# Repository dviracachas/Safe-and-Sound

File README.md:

# Intercomunicador Safe & Sound 🏍
En este repositorio se encuentra el desarrollo de la propuesta de proyecto realizada para la asignatura de Sistemas Embebidos de la Universidad Nacional de Colombia, la cual consiste en un intercomunicador para motocicletas que cuente con funcionalidades orientadas a la seguridad de sus usuarios.

## Equipo de trabajo
* Juan Gabriel Barrera Barrera
* Juan José Forero Bernal
* Camilo Andrés Jaimes Reyes
* David Santiago Viracachá Suárez

## Descripción general
El intercomunicador Safe & Sound es un producto para motociclistas que buscan comunicarse con sus pasajeros o hacer uso de funciones de audio por medio de su teléfono celular, como lo puede ser recibir indicaciones de alguna aplicación de mapas. Además, es un producto que busca la seguridad del usuario, emitiendo alertas de velocidad e implementando detección de accidentes para realizar llamadas de emergencia haciendo uso del teléfono.

## Requerimientos funcionales
* Conectarse a otro dispositivo igual o un teléfono mediante Bluetooth
* Transmitir y/o recibir audio con los dispositivos conectados
* Procesamiento de señales dadas por sensores
* Emitir alertas de velocidad al usuario
* Detectar cambios repentinos de velocidad
* Comunicación con emergencias por medio de conexión con celular

## Requerimientos no funcionales
* Dispositivo pequeño adaptable a cascos para motocicletas
* Amigable al usuario
* Duración de la batería
* Cumplir con estándares de audio Bluetooth y compatibilidad electromagnética
* Cumplir con normas establecidas para circuitos impresos

## Diagrama de bloques

## Diagrama de funcionamiento
[Diagrama de funcionamiento](Imagenes/Funcionamiento_safe_and_sound.pdf)

### Descripción del Hardware
Una vez identificadas las funciones y los requerimientos del intercomunicador a realizar se escogen los compontes básicos, estos son:

Componentes Básicos:
* ESP32-WROOM-32
* Acelerómetro ADXL335.
* Batería de litio de 3.7V y 280mAh.
* Amplificador de Audio MAX98357 I2S 3W clase D
* Módulo Micrófono Mems I2s Inmp441
* Mini Altavoces.
* Conectores de diversos tipos.
* Resistores.
* Capacitores
* Potenciómetro.
* Pulsadores.
* Leds.
* Conector Micro-USB hembra.
* Switch Deslizante.

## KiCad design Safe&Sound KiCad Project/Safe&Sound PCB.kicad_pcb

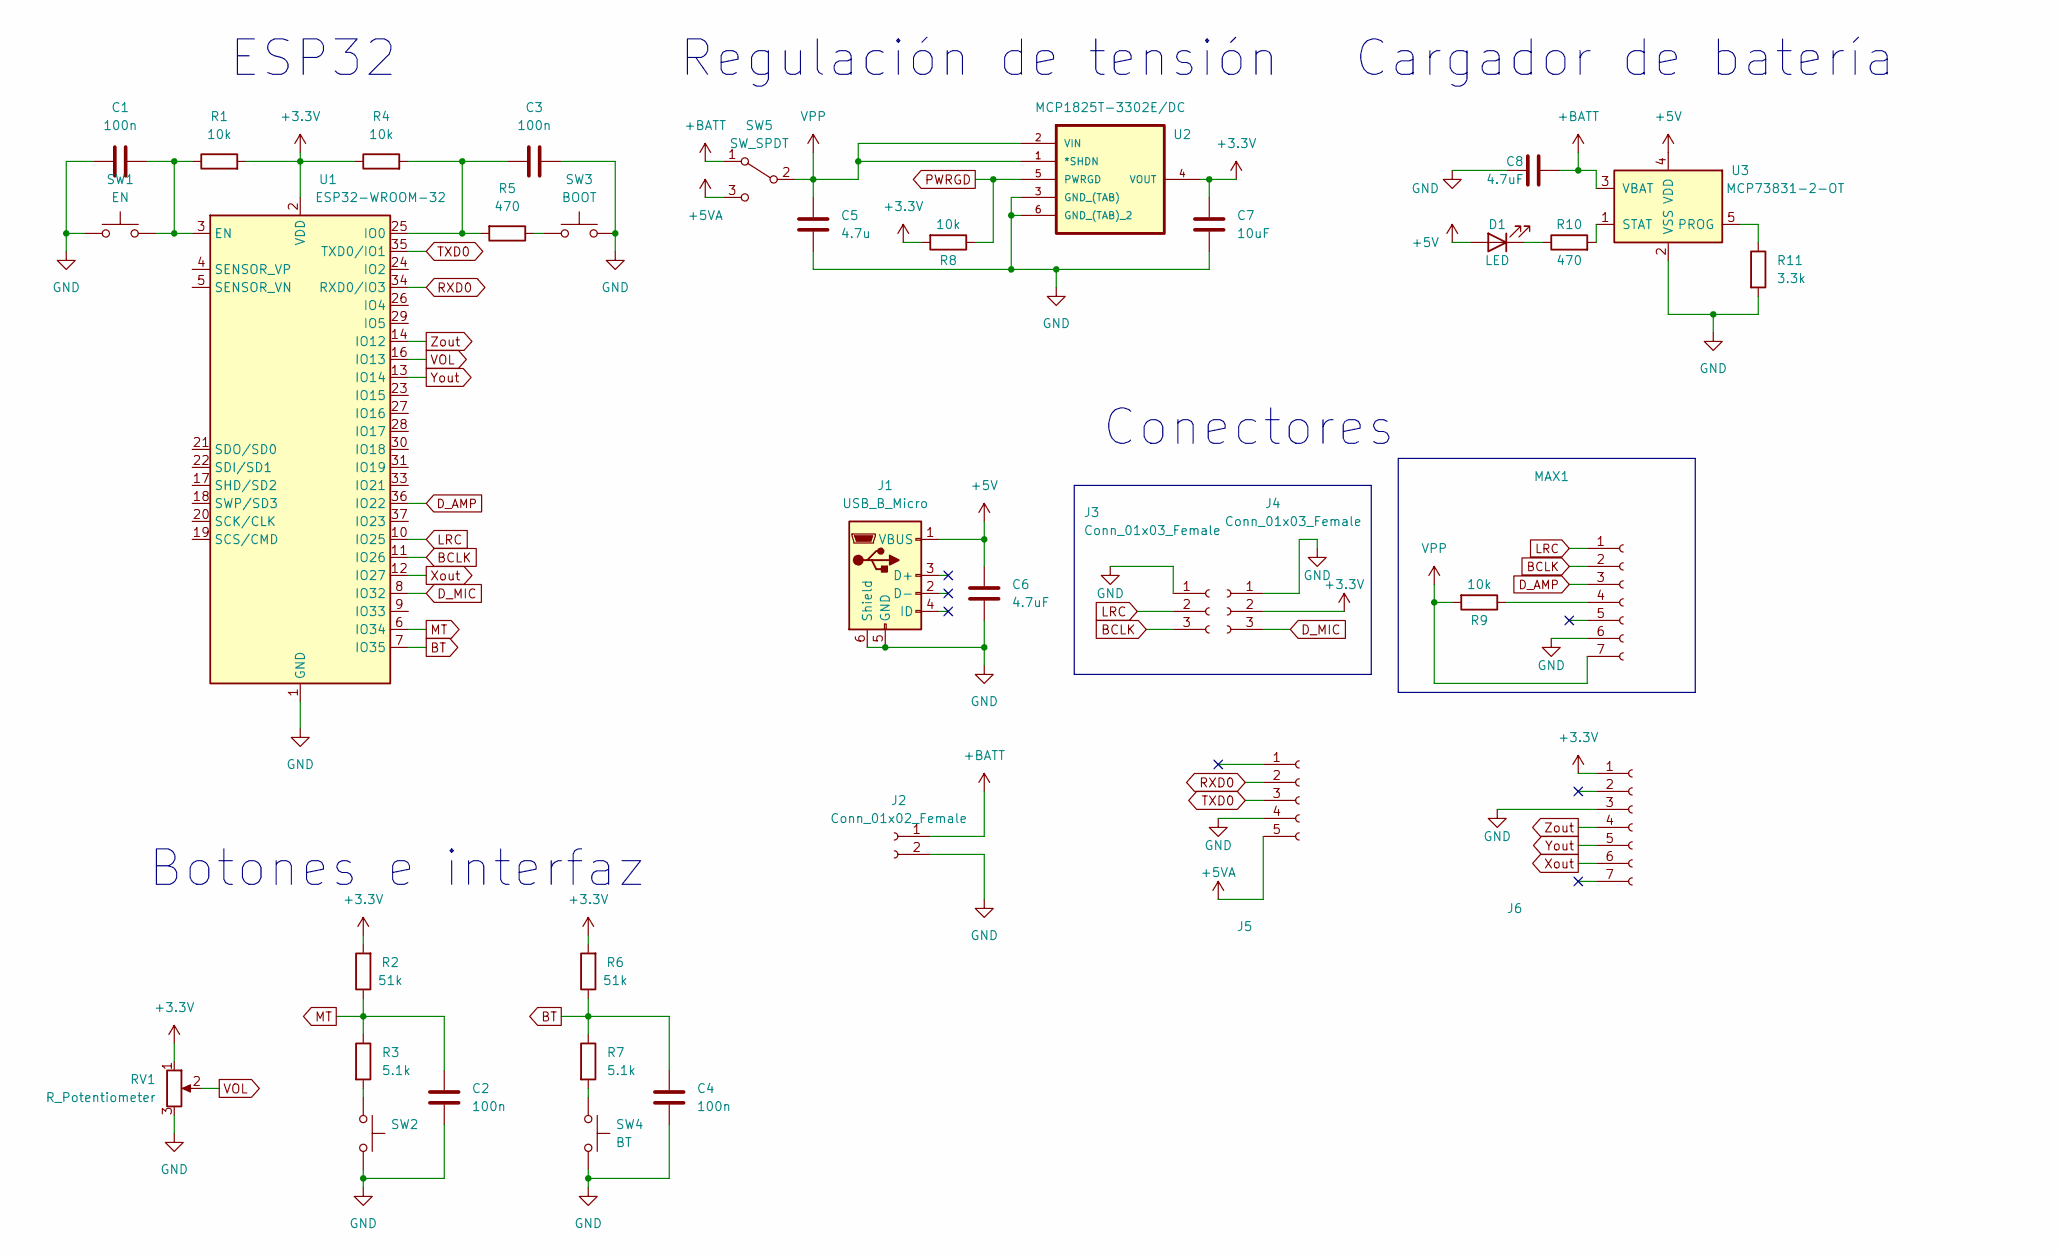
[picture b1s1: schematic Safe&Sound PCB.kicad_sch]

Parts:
C1, C2, C3, C4: 100n; C_0805_2012Metric_Pad1.18x1.45mm_HandSolder
C5: 4.7u; C_0805_2012Metric_Pad1.18x1.45mm_HandSolder
C6, C8: 4.7uF; C_0805_2012Metric_Pad1.18x1.45mm_HandSolder
C7: 10uF; C_0805_2012Metric_Pad1.18x1.45mm_HandSolder
D1: LED; LED_0805_2012Metric_Pad1.15x1.40mm_HandSolder
J1: USB_B_Micro; USB_Micro-B_Molex-105017-0001
J2: Conn_01x02_Female; JST_PH_S2B-PH-K_1x02_P2.00mm_Horizontal
J3, J4: Conn_01x03_Female; PinSocket_1x03_P2.54mm_Vertical
J5, J6: (no value)
MAX1: (no value)
R1, R4, R8, R9: 10k; R_0805_2012Metric_Pad1.20x1.40mm_HandSolder
R2, R6: 51k; R_0805_2012Metric_Pad1.20x1.40mm_HandSolder
R3, R7: 5.1k; R_0805_2012Metric_Pad1.20x1.40mm_HandSolder
R5, R10: 470; R_0805_2012Metric_Pad1.20x1.40mm_HandSolder
R11: 3.3k; R_0805_2012Metric_Pad1.20x1.40mm_HandSolder
RV1: R_Potentiometer; Potentiometer_ACP_CA6-VSMD_Vertical
SW1: EN; SW_SPST_EVQQ2
SW2: SW_SPST_EVQQ2
SW3: BOOT; SW_SPST_EVQQ2
SW4: BT; SW_SPST_EVQQ2
SW5: SW_SPDT; SW_CuK_OS102011MA1QN1_SPDT_Angled
U1: ESP32-WROOM-32
U2: MCP1825T-3302E/DC; SOT230P700X180-6N; MPN MCP1825T-3302E/DC
U3: MCP73831-2-OT; SOT-23-5_HandSoldering

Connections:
+3V3: C7.1, J4.2, J6.1, R1.2, R2.2, R4.1, R6.2, R8.2, RV1.1, U1.2 (VDD), U2.4 (VOUT)
+5V: C6.1, D1.2 (A), J1.1 (VBUS), U3.4 (VDD)
+5VA: J5.5, SW5.3 (C)
+BATT: C8.2, J2.1, SW5.1 (A), U3.3 (VBAT)
BCLK: J3.3, MAX1.2, U1.11 (IO26)
BT: C4.2, R6.1, R7.1, U1.7 (IO35)
D_AMP: MAX1.3, U1.36 (IO22)
D_MIC: J4.3, U1.8 (IO32)
GND: C1.1, C2.1, C3.2, C4.1, C5.2, C6.2, C7.2, C8.1, J1.5 (GND), J1.6 (Shield), J2.2, J3.1, J4.1, J5.4, J6.3, MAX1.6, R11.2, RV1.3, SW1.1, SW2.2, SW3.2, SW4.2, U1.1 (GND), U1.15 (GND), U1.38 (GND), U1.39 (GND), U2.3 (GND_(TAB)), U2.6 (GND_(TAB)_2), U3.2 (VSS)
LRC: J3.2, MAX1.1, U1.10 (IO25)
MT: C2.2, R2.1, R3.1, U1.6 (IO34)
unnamed: C1.2, R1.1, SW1.2, U1.3 (EN)
unnamed: C3.1, R4.2, R5.2, U1.25 (IO0)
unnamed: D1.1 (K), R10.1
unnamed: MAX1.4, R9.1
unnamed: R3.2, SW2.1
unnamed: R5.1, SW3.1
unnamed: R7.2, SW4.1
unnamed: R10.2, U3.1 (STAT)
unnamed: R11.1, U3.5 (PROG)
PWRGD: R8.1, U2.5 (PWRGD)
RXD0: J5.2, U1.34 (RXD0/IO3)
TXD0: J5.3, U1.35 (TXD0/IO1)
VOL: RV1.2, U1.16 (IO13)
VPP: C5.1, MAX1.7, R9.2, SW5.2 (B), U2.1 (*SHDN), U2.2 (VIN)
Xout: J6.6, U1.12 (IO27)
Yout: J6.5, U1.13 (IO14)
Zout: J6.4, U1.14 (IO12)

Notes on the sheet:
Cargador de batería
Botones e interfaz
ESP32
Conectores
Regulación de tensión

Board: 2 copper layers, 36 parts (29 on the bottom side), 28 nets, no tracks yet.

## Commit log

2022-03-26 Apertura de la documentación
    - Se agrega la primera versión de la documentación incluyendo descripción básica, funcional y primer acercamiento a implementación mediante diagrama de bloques.
2022-04-17 Esquemático de Alimentación
    - Se crea el proyecto de KiCad y se agrega la primera versión del sistema de alimentación, que incluye conectores de batería y cargador (microusb-b), circuito de carga y circuito regulador de voltaje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
2022-04-17 Puerto de programación
    - Se añade un socket para hacer uso de un módulo USB a TTL con CP2102 para la programación del módulo ESP32-WROOM-32.
2022-04-26 Esquemático micrófono y amplificador
2022-04-28 Unificación de relojes
2022-04-28 relojes
2022-04-30 Acelerómetro y cambio regulador
    - Se añada el conector de acelerómetro
    - Se cambia el regulador LD1117 por el MCP1825 y se agrega a la librería del proyecto
    - Se modifica el botón de GPIO0 para asegurar que se encuentre en pull-up externamente
2022-04-30 Esquemático unido
    - Se unieron los diferentes esquemáticos realizados en uno solo.
2022-05-01 Asignación de huellas y correcciones
    - Se realizan correcciones
    - Se agregan huellas provisionales de los componentes
2022-05-01 Organización preliminar de componentes
2022-05-02 huella switch
2022-05-05 PCB y archivos de fabricación
    - Se agrega el LED de usuario
    - Se trazan las rutas de la PCB
    - Se generan los archivos de fabricación
2022-05-09 PCB con zona GND y archivos de fabricación
    - Se actualizan los archivos de fabricación de la PCB.
    - Se aumentan distancias entre ciertas pistas para evitar problemas de tolerancia.
2022-05-11 Add files via upload
    Se agrega el diagrama de funcionamiento del intercomunicador
2022-05-11 Se agrego el diagrama de funcionamiento al Readme
2022-05-11 Update README.md
    Se agregó el diagrama de funcionamiento al Readme
2022-05-11 Eliminación carpeta
2022-05-12 Se añadieron marcas de no conectado a los pines que no se usaran
2022-06-17 Inicio de documentación
2022-06-17 Auto stash before merge of "main" and "origin/main"
2022-06-17 Carga de imágenes
2022-06-17 Ajuste de documentación
    Se ajustaron las imágenes en el respectivo orden
2022-06-17 Ajuste de documentación
    Se adjuntaron y organizaron las imágenes.
2022-07-01 Actualización Diagrama de bloques
2022-07-05 img funciones
2022-07-05 product
